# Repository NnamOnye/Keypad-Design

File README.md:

# Keypad-PCB(KiCAD ECAD)
# Developed by M.O
# This is a keypad system using cherry switches(MX1A-11NN), an esp32(ESP32-S2-SAOLA-1R), an LCD display, and a LDO(Low Drop Out regulator).
# This keypad can be used/intergrated into many different applications (calculator,biometric lock,etc..)
# KiCAD will be needed for this project if replicating.
# KiCAD Download --> https://www.kicad.org/download/

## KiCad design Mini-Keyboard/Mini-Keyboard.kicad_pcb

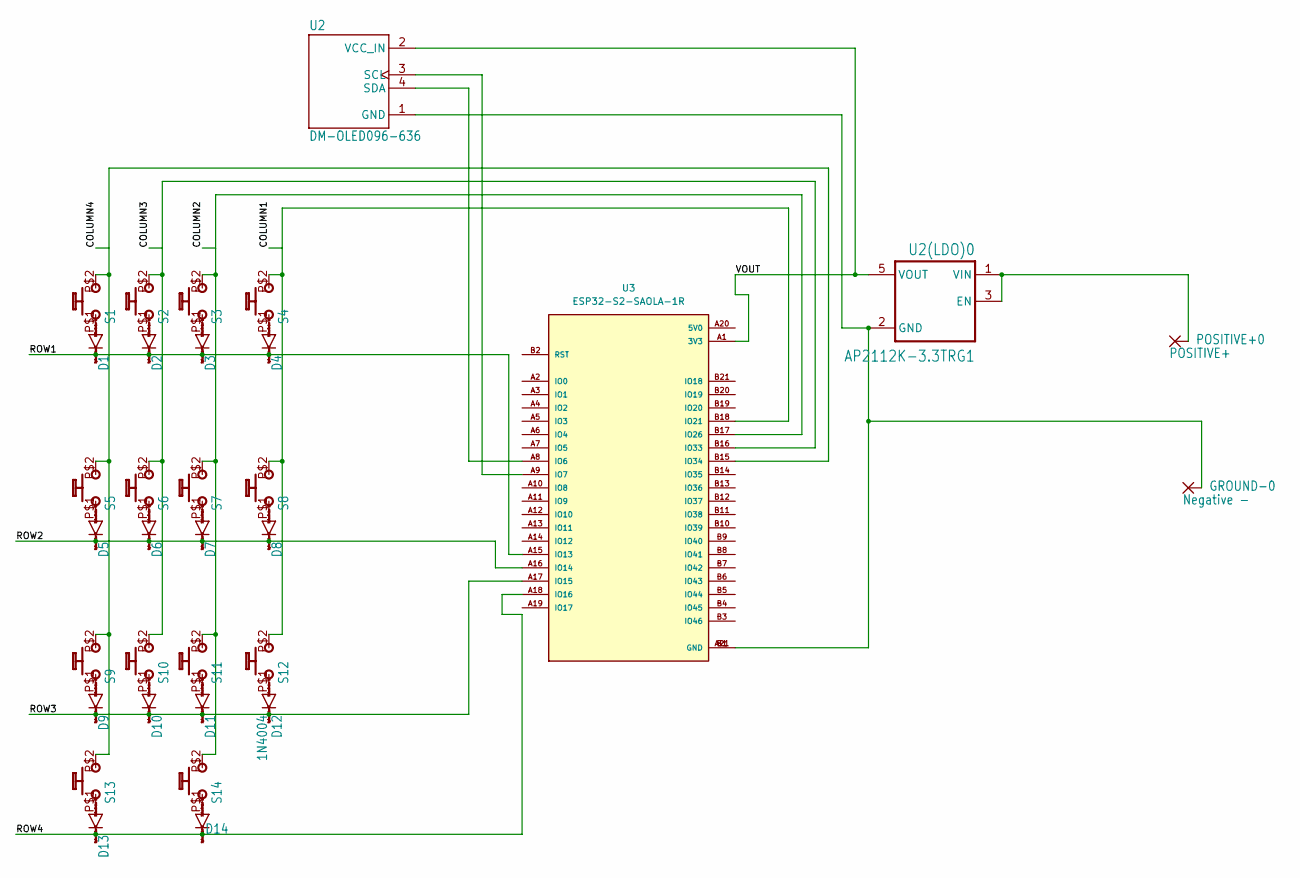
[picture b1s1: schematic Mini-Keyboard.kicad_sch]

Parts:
D1, D2, D3, D4, D5, D6, D7, D8, D9, D10, D11, D12, D13, D14: 1N4004; DO41-10
GROUND-0: Negative -; SMD2,54-5,08
POSITIVE+0: POSITIVE+; SMD2,54-5,08
S1, S2, S3, S4, S5, S6, S7, S8, S9, S10, S11, S12, S13, S14: MX1A-11NN; CHERRY_MX1A-11NN_SWITCH
U2: DM-OLED096-636; MODULE_DM-OLED096-636
U2(LDO)0: AP2112K-3.3TRG1; SOT95P285X140-5N
U3: ESP32-S2-SAOLA-1R; XCVR_ESP32-S2-SAOLA-1R; PARTREV 1.2

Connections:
/ROW1: D1.C, D2.C, D3.C, D4.C, U3.A15 (IO13)
/ROW2: D5.C, D6.C, D7.C, D8.C, U3.A16 (IO14)
/ROW3: D9.C, D10.C, D11.C, D12.C, U3.A17 (IO15)
/ROW4: D13.C, D14.C, U3.A18 (IO16)
/VOUT: U2.2 (VCC_IN), U2(LDO)0.5 (VOUT), U3.A1 (3V3)
unnamed: GROUND-0.1, U2.1 (GND), U2(LDO)0.2 (GND), U3.A21 (GND), U3.B1 (GND)
unnamed: POSITIVE+0.1, U2(LDO)0.1 (VIN), U2(LDO)0.3 (EN)
unnamed: D1.A, S1.P$1
unnamed: S1.P$2 (S), S5.P$2 (S), S9.P$2 (S), S13.P$2 (S), U3.B15 (IO34)
unnamed: D2.A, S2.P$1
unnamed: D3.A, S3.P$1
unnamed: D4.A, S4.P$1
unnamed: D5.A, S5.P$1
unnamed: D6.A, S6.P$1
unnamed: D7.A, S7.P$1
unnamed: D8.A, S8.P$1
unnamed: D9.A, S9.P$1
unnamed: D10.A, S10.P$1
unnamed: S2.P$2 (S), S6.P$2 (S), S10.P$2 (S), U3.B16 (IO33)
unnamed: D11.A, S11.P$1
unnamed: S3.P$2 (S), S7.P$2 (S), S11.P$2 (S), S14.P$2 (S), U3.B17 (IO26)
unnamed: D12.A, S12.P$1
unnamed: S4.P$2 (S), S8.P$2 (S), S12.P$2 (S), U3.B18 (IO21)
unnamed: D13.A, S13.P$1
unnamed: D14.A, S14.P$1
unnamed: U2.3 (SCL), U3.A9 (IO7)
unnamed: U2.4 (SDA), U3.A8 (IO6)

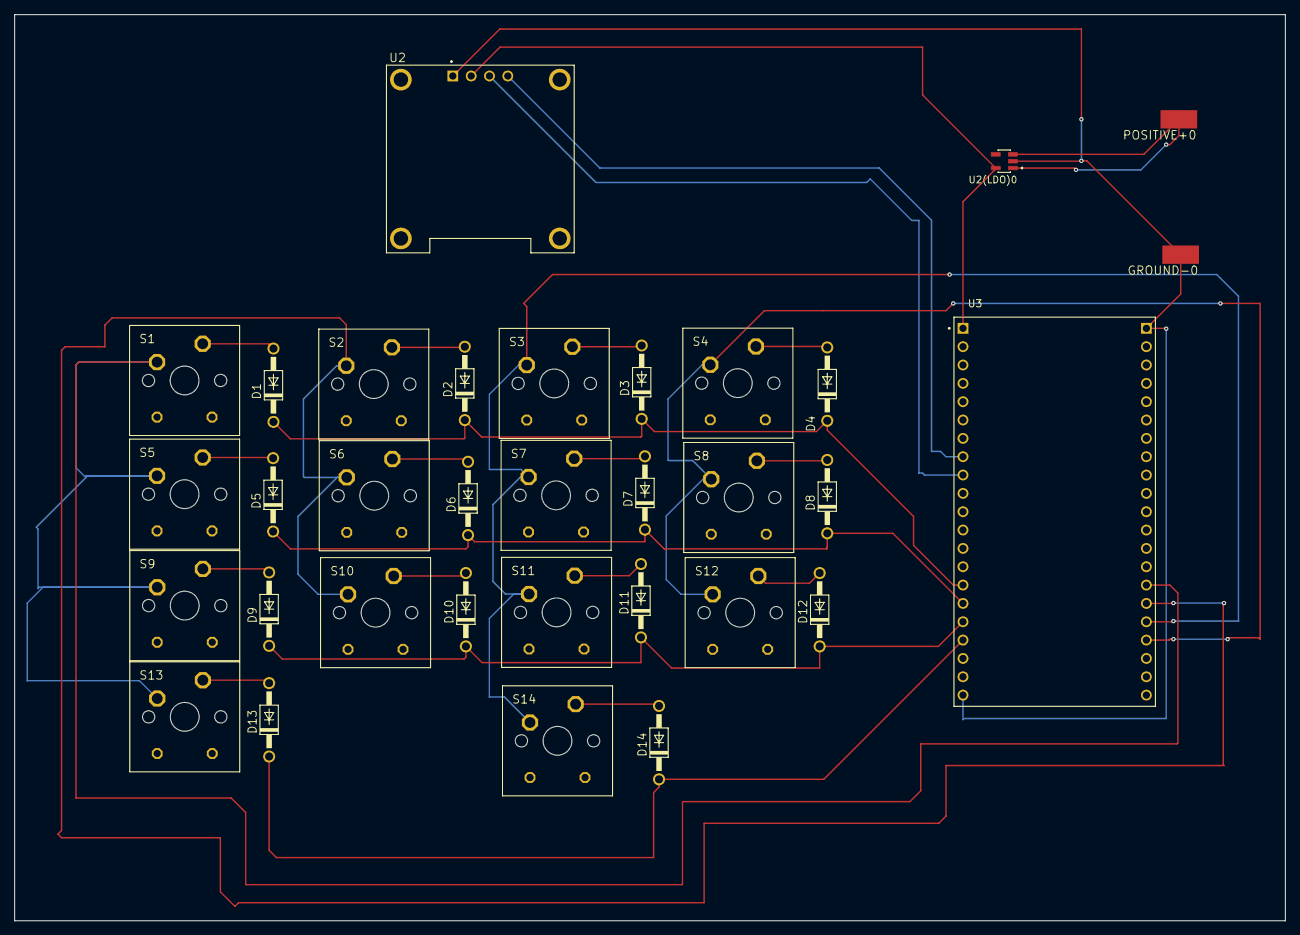
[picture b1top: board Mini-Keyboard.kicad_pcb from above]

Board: 2 copper layers, 176.0 x 125.5 mm, 33 parts (0 on the bottom side), 27 nets.

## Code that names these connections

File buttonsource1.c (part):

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}

// Define row GPIO pins
#define ROW1_GPIO GPIO_NUM_1
#define ROW2_GPIO GPIO_NUM_2
#define ROW3_GPIO GPIO_NUM_3
#define ROW4_GPIO GPIO_NUM_4


// Define column GPIO pins
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void configure_buttons() {
	//Row Configuration
    gpio_config_t row1_conf = {
    .pin_bit_mask = (1ULL << ROW1_GPIO),
    .mode = GPIO_MODE_INPUT,
    .pull_up_en = GPIO_PULLUP_ENABLE,
    .intr_type = GPIO_INTR_DISABLE
	};
	
	gpio_config_t row2_conf = {
	    .pin_bit_mask = (1ULL << ROW2_GPIO),
	    .mode = GPIO_MODE_INPUT,
	    .pull_up_en = GPIO_PULLUP_ENABLE,
	    .intr_type = GPIO_INTR_DISABLE
	};
	
	gpio_config_t row3_conf = {
	    .pin_bit_mask = (1ULL << ROW3_GPIO),
	    .mode = GPIO_MODE_INPUT,
	    .pull_up_en = GPIO_PULLUP_ENABLE,
	    .intr_type = GPIO_INTR_DISABLE
	};
	
	gpio_config_t row4_conf = {
	    .pin_bit_mask = (1ULL << ROW4_GPIO),
	    .mode = GPIO_MODE_INPUT,
	    .pull_up_en = GPIO_PULLUP_ENABLE,
	    .intr_type = GPIO_INTR_DISABLE
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        }

        // Check if any row is pressed (low level)
        if (gpio_get_level(ROW1_GPIO) == 0) {
            printf("Button in column %d, row 1 pressed\n", col);
        }
        if (gpio_get_level(ROW2_GPIO) == 0) {
            printf("Button in column %d, row 2 pressed\n", col);
        }
        if (gpio_get_level(ROW3_GPIO) == 0) {
            printf("Button in column %d, row 3 pressed\n", col);
        }
        if (gpio_get_level(ROW4_GPIO) == 0) {
            printf("Button in column %d, row 4 pressed\n", col);
        }
    }
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}


#define WAKEUP_MASK  ((1ULL << ROW1_GPIO) | (1ULL << ROW2_GPIO) | (1ULL << ROW3_GPIO) | (1ULL << ROW4_GPIO) | \
                      (1ULL << COL1_GPIO) | (1ULL << COL2_GPIO) | (1ULL << COL3_GPIO) | (1ULL << COL4_GPIO)|(1ULL << TOUCHOUT_GPIO))
                      //This is a bitmask that includes all the GPIOs of the keypad matrix (rows and columns

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    for (int i = sleep_delay_sec; i > 0; i--) {
		
        // Check if any key GPIO is LOW (pressed)
        if ((gpio_get_level(ROW1_GPIO) == 0) || (gpio_get_level(ROW2_GPIO) == 0) || 
            (gpio_get_level(ROW3_GPIO) == 0) || (gpio_get_level(ROW4_GPIO) == 0) ||
            (gpio_get_level(COL1_GPIO) == 0) || (gpio_get_level(COL2_GPIO) == 0) ||
            (gpio_get_level(COL3_GPIO) == 0) || (gpio_get_level(COL4_GPIO) == 0)||(gpio_get_level(TOUCHOUT_GPIO) == 0)) {
            cancel_sleep = true;
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
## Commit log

2025-03-31 How to Import External Libraries into KiCad
2025-03-31 README.md
2025-03-31 External Library
2025-03-31 PCB SCHEMATIC FILE
    PCB SCHEMATIC FILE
2025-03-31 EXTERNAL LIBRARIES
    EXTERNAL LIBRARIES (IF NEEDED)
2025-04-18 Firmware(ESP32-S2-Saola-1R)
2025-04-18 buttonsource.c
2025-08-22 Delete buttonsource1.c
    firmware depends on the application,
    i.e "keyboard, calculator,etc.."
    i'll leave it up to the implementor to decide how they will write their code.
2025-08-22 how-to-import.pdf
